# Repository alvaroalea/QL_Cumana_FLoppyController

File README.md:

# Cumana Disk Interface for Sinclair QL

A clone of the Cumana's Floppy Disk Interface for Sinclair QL
(PCB issue 1, ROM version 1.14)

This board has been suessfully tested with ROM 1.16, real floppy disc and gotek.

### The Board

There are two knows version of the ROM, 1.14 and 1.16. unknow diferences between revisiones of ROM.

It use the standar stugart conector, so a plain cable can have up to 4 disk drives, that shall be correctly configured as DS0, DS1, DS2 or DS3.

It use a WD1770 disc controller, but is compatible with WD1772 (you can need to configure start speed), WD1773 is not compatible.

Be aware, when install the transistor, is C,B,E with C near the 7805.

Thanks to Minialler from retrowiki for providing me with a board so I can take pictures and check tracks  that allow me to capture the schema.

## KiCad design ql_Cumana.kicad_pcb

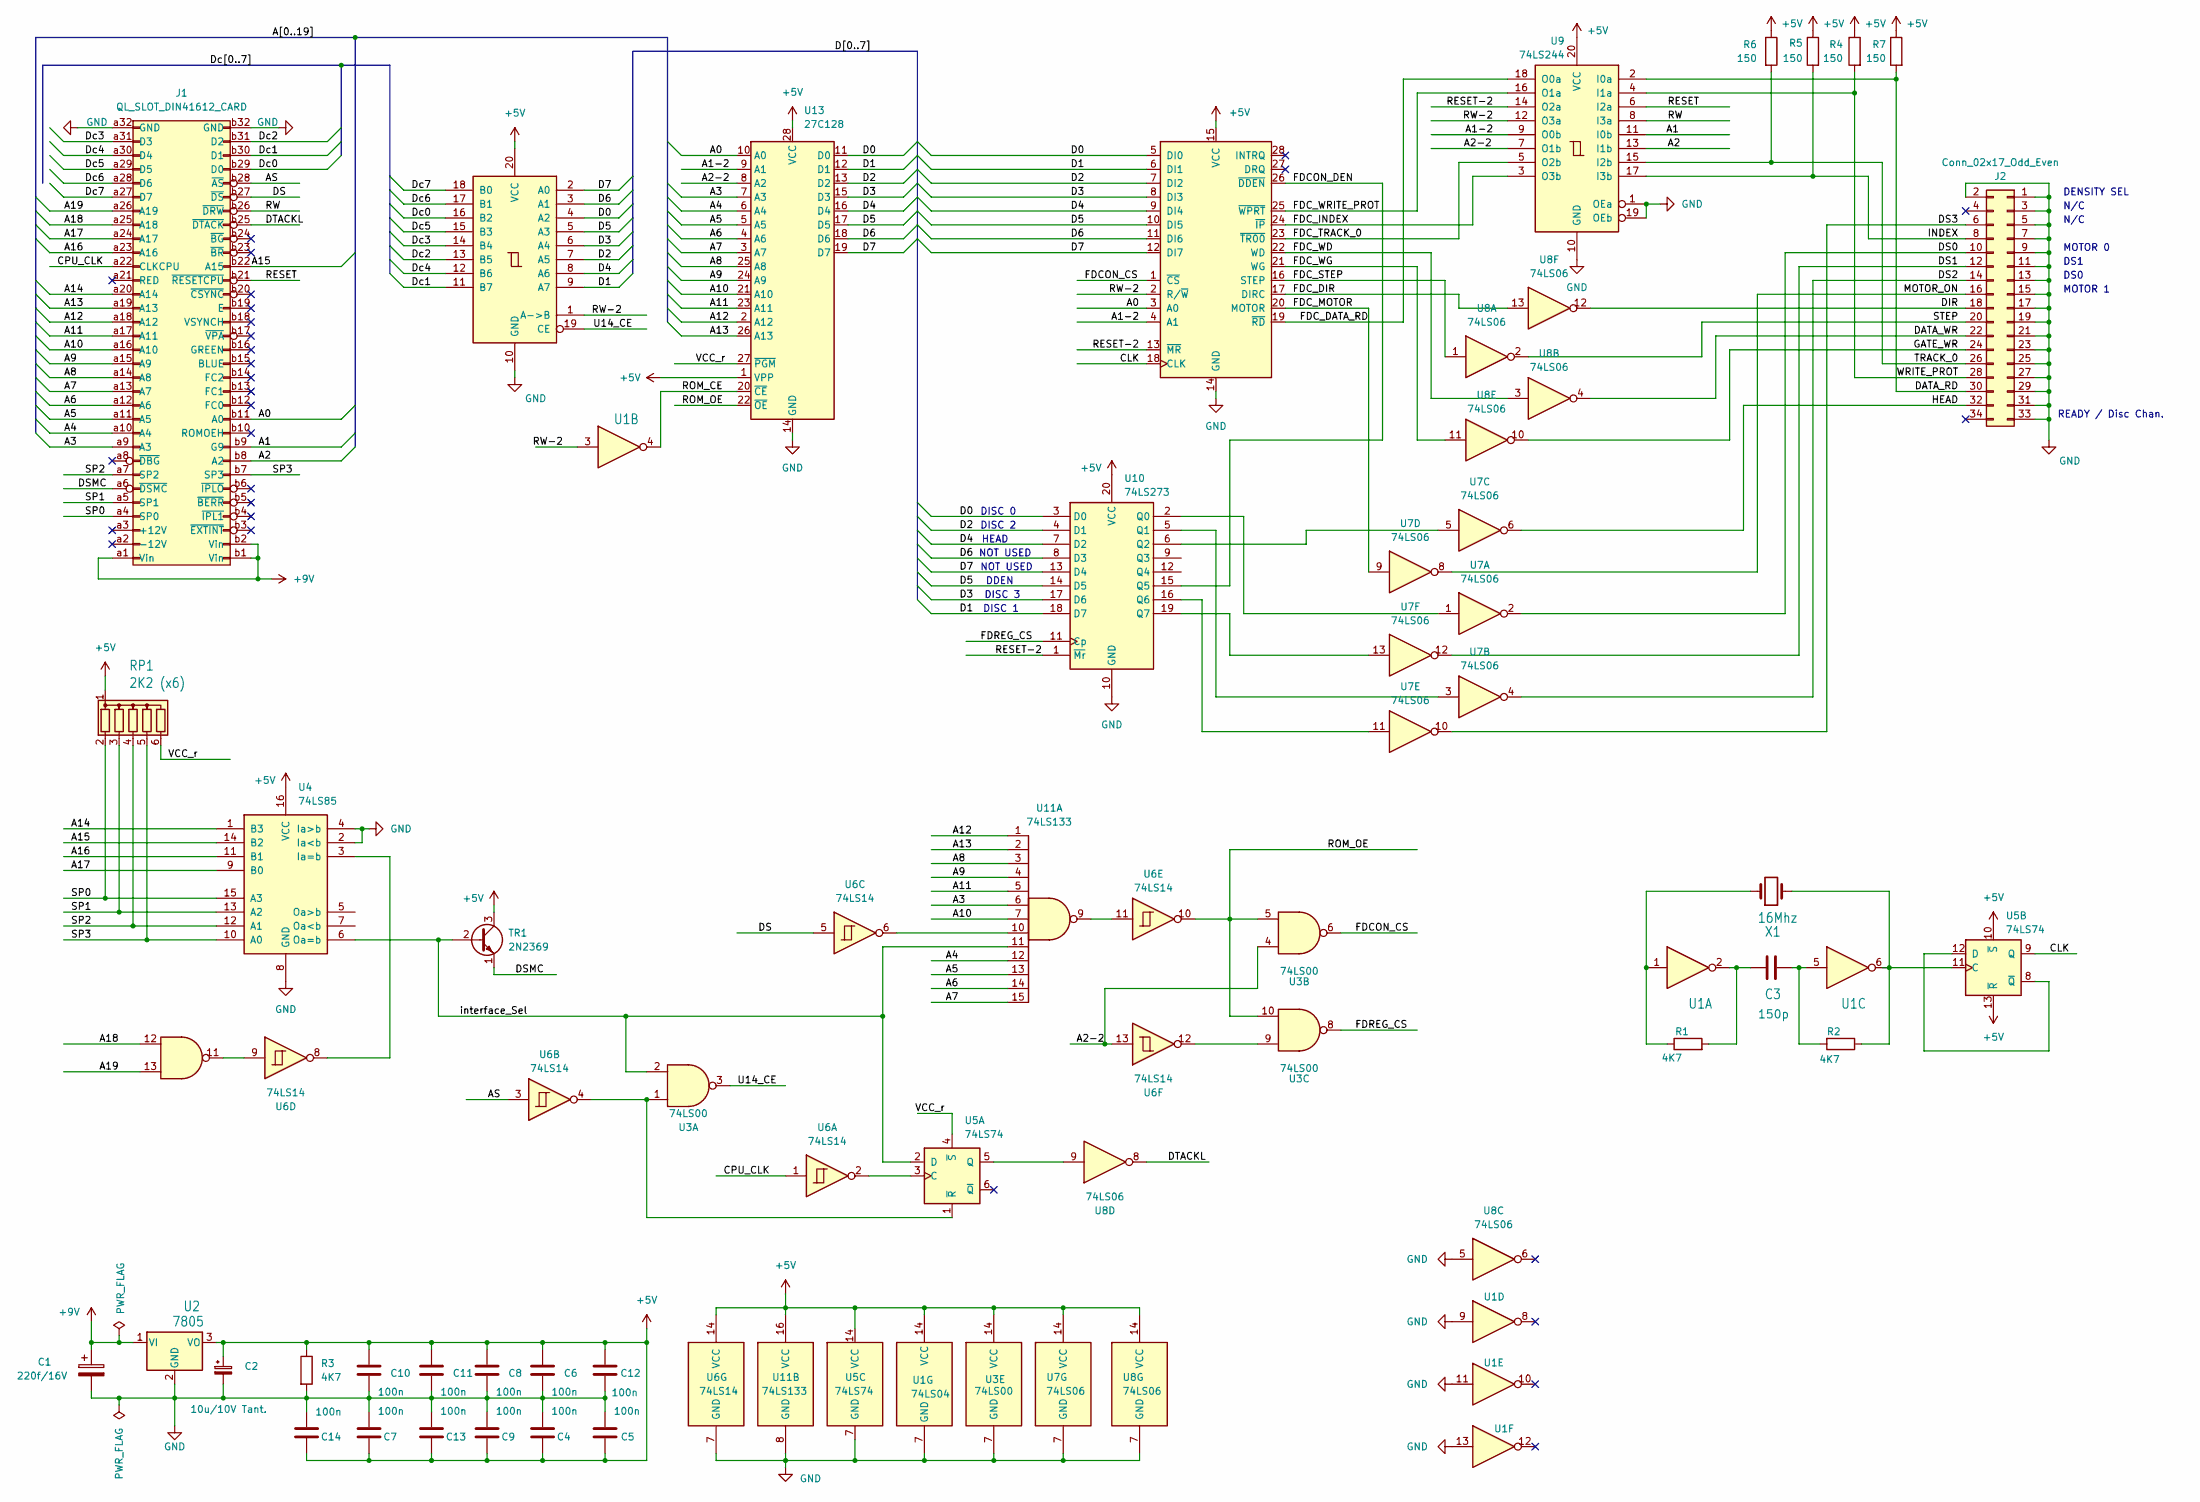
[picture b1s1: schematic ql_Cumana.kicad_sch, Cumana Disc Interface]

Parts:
C1: 220f/16V; CP_Radial_D8.0mm_P5.00mm
C2: 10u/10V Tant.; C_Disc_D7.0mm_W2.5mm_P5.00mm
C3: 150p; C_Disc_D7.0mm_W2.5mm_P5.00mm
C4, C5, C6, C7, C8, C9, C10, C11, C12, C13, C14: 100n; C_Disc_D7.0mm_W2.5mm_P5.00mm
J1: QL_SLOT_DIN41612_CARD; DIN41612_B_2x32_Female_Horizontal_THT
J2: Conn_02x17_Odd_Even; IDC-Header_2x17_P2.54mm_Latch_Horizontal
R1, R2, R3: 4K7; R_Axial_DIN0207_L6.3mm_D2.5mm_P10.16mm_Horizontal
R4, R5, R6, R7: 150; R_Axial_DIN0207_L6.3mm_D2.5mm_P10.16mm_Horizontal
RP1: 2K2 (x6); R_Array_SIP6
TR1: 2N2369; TO-92S_Wide
U1: 74LS04; DIP-14_W7.62mm
U2: 7805; TO-220-3_Horizontal_TabDown
U3: 74LS00; DIP-14_W7.62mm
U4: 74LS85; DIP-16_W7.62mm
U5: 74LS74; DIP-14_W7.62mm
U6: 74LS14; DIP-14_W7.62mm
U7, U8: 74LS06; DIP-14_W7.62mm
U9: 74LS244; DIP-20_W7.62mm
U10: 74LS273; DIP-20_W7.62mm
U11: 74LS133; DIP-16_W7.62mm
U12: FDC_WD1770; DIP-28_W15.24mm_Socket
U13: 27C128; DIP-28_W15.24mm_Socket
U14: 74LS245; DIP-20_W7.62mm
X1: 16Mhz; Crystal_HC18-U_Horizontal

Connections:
+5V: C2.1, C4.1, C5.1, C6.1, C7.1, C8.1, C9.1, C10.1, C11.1, C12.1, C13.1, C14.1, R3.1, R4.1, R5.1, R6.1, R7.1, RP1.1 (common), TR1.3 (C), U1.14 (VCC), U2.3 (VO), U3.14 (VCC), U4.16 (VCC), U5.10 (~S), U5.13 (~R), U5.14 (VCC), U6.14 (VCC), U7.14 (VCC), U8.14 (VCC), U9.20 (VCC), U10.20 (VCC), U11.16 (VCC), U12.15 (VCC), U13.1 (VPP), U13.28 (VCC), U14.20 (VCC)
+9V: C1.1, J1.a1 (Vin), J1.b1 (Vin), J1.b2 (Vin), U2.1 (VI)
/A0: J1.b11 (A0), U12.3 (A0), U13.10 (A0)
/A1: J1.b9 (G9), U9.11 (I0b)
/A1-2: U9.9 (O0b), U12.4 (A1), U13.9 (A1)
/A2: J1.b8 (A2), U9.13 (I1b)
/A2-2: U3.4, U6.13, U9.7 (O1b), U13.8 (A2)
/A3: J1.a9 (A3), U11.6, U13.7 (A3)
/A4: J1.a10 (A4), U11.12, U13.6 (A4)
/A5: J1.a11 (A5), U11.13, U13.5 (A5)
/A6: J1.a12 (A6), U11.14, U13.4 (A6)
/A7: J1.a13 (A7), U11.15, U13.3 (A7)
/A8: J1.a14 (A8), U11.3, U13.25 (A8)
/A9: J1.a15 (A9), U11.4, U13.24 (A9)
/A10: J1.a16 (A10), U11.7, U13.21 (A10)
/A11: J1.a17 (A11), U11.5, U13.23 (A11)
/A12: J1.a18 (A12), U11.1, U13.2 (A12)
/A13: J1.a19 (A13), U11.2, U13.26 (A13)
/A14: J1.a20 (A14), U4.1 (B3)
/A15: J1.b22 (A15), U4.14 (B2)
/A16: J1.a23 (A16), U4.11 (B1)
/A17: J1.a24 (A17), U4.9 (B0)
/A18: J1.a25 (A18), U3.12
/A19: J1.a26 (A19), U3.13
/AS: J1.b28 (~AS), U6.3
/CLK: U5.9 (Q), U12.18 (CLK)
/CPU_CLK: J1.a22 (CLKCPU), U6.1
/D0: U10.3 (D0), U12.5 (DI0), U13.11 (D0), U14.4 (A2)
/D1: U10.18 (D7), U12.6 (DI1), U13.12 (D1), U14.9 (A7)
/D2: U10.4 (D1), U12.7 (DI2), U13.13 (D2), U14.7 (A5)
/D3: U10.17 (D6), U12.8 (DI3), U13.15 (D3), U14.6 (A4)
/D4: U10.7 (D2), U12.9 (DI4), U13.16 (D4), U14.8 (A6)
/D5: U10.14 (D5), U12.10 (DI5), U13.17 (D5), U14.5 (A3)
/D6: U10.8 (D3), U12.11 (DI6), U13.18 (D6), U14.3 (A1)
/D7: U10.13 (D4), U12.12 (DI7), U13.19 (D7), U14.2 (A0)
/DATA_RD: J2.30, R7.2, U9.2 (I0a)
/DATA_WR: J2.22, U8.4
/DIR: J2.18, U8.12
/DS: J1.b27 (~DS), U6.5
/DS0: J2.10, U7.2
/DS1: J2.12, U7.12
/DS2: J2.14, U7.4
/DS3: J2.6, U7.10
/DSMC: J1.a6 (~DSMC), TR1.1 (E)
/DTACKL: J1.b25 (~DTACK), U8.8
/Dc0: J1.b29 (D0), U14.16 (B2)
/Dc1: J1.b30 (D1), U14.11 (B7)
/Dc2: J1.b31 (D2), U14.13 (B5)
/Dc3: J1.a31 (D3), U14.14 (B4)
/Dc4: J1.a30 (D4), U14.12 (B6)
/Dc5: J1.a29 (D5), U14.15 (B3)
/Dc6: J1.a28 (D6), U14.17 (B1)
/Dc7: J1.a27 (D7), U14.18 (B0)
/FDCON_CS: U3.6, U12.1 (~CS)
/FDCON_DEN: U10.15 (Q5), U12.26 (~DDEN)
/FDC_DATA_RD: U9.18 (O0a), U12.19 (~RD)
/FDC_DIR: U8.13, U12.17 (DIRC)
/FDC_INDEX: U9.3 (O3b), U12.24 (~IP)
/FDC_MOTOR: U7.9, U12.20 (MOTOR)
/FDC_STEP: U8.1, U12.16 (STEP)
/FDC_TRACK_0: U9.5 (O2b), U12.23 (~TR00)
/FDC_WD: U8.3, U12.22 (WD)
/FDC_WG: U8.11, U12.21 (WG)
/FDC_WRITE_PROT: U9.16 (O1a), U12.25 (~WPRT)
/FDREG_CS: U3.8, U10.11 (Cp)
/GATE_WR: J2.24, U8.10
/HEAD: J2.32, U7.6
/INDEX: J2.8, R5.2, U9.17 (I3b)
/MOTOR_ON: J2.16, U7.8
/RESET: J1.b21 (~RESETCPU), U9.6 (I2a)
/RESET-2: U9.14 (O2a), U10.1 (~Mr), U12.13 (~MR)
/ROM_CE: U1.4, U13.20 (~CE)
/ROM_OE: U3.5, U3.10, U6.10, U13.22 (~OE)
/RW: J1.b26 (~DRW), U9.8 (I3a)
/RW-2: U1.3, U9.12 (O3a), U12.2 (R/~W), U14.1 (A->B)
/SP0: J1.a4 (SP0), RP1.2 (R1), U4.15 (A3)
/SP1: J1.a5 (SP1), RP1.3 (R2), U4.13 (A2)
/SP2: J1.a7 (SP2), RP1.4 (R3), U4.12 (A1)
/SP3: J1.b7 (SP3), RP1.5 (R4), U4.10 (A0)
/STEP: J2.20, U8.2
/TRACK_0: J2.26, R6.2, U9.15 (I2b)
/U14_CE: U3.3, U14.19 (CE)
/VCC_r: RP1.6 (R5), U5.4 (~S), U13.27 (~PGM)
/WRITE_PROT: J2.28, R4.2, U9.4 (I1a)
/interface_Sel: TR1.2 (B), U3.2, U4.6 (Oa=b), U5.2 (D), U11.11
GND: C1.2, C2.2, C4.2, C5.2, C6.2, C7.2, C8.2, C9.2, C10.2, C11.2, C12.2, C13.2, C14.2, J1.a32 (GND), J1.b32 (GND), J2.1, J2.2, J2.3, J2.5, J2.7, J2.9, J2.11, J2.13, J2.15, J2.17, J2.19, J2.21, J2.23, J2.25, J2.27, J2.29, J2.31, J2.33, R3.2, U1.7 (GND), U1.9, U1.11, U1.13, U2.2 (GND), U3.7 (GND), U4.2 (Ia<b), U4.4 (Ia>b), U4.8 (GND), U5.7 (GND), U6.7 (GND), U7.7 (GND), U8.5, U8.7 (GND), U9.1 (OEa), U9.10 (GND), U9.19 (OEb), U10.10 (GND), U11.8 (GND), U12.14 (GND), U13.14 (GND), U14.10 (GND)
unnamed: C3.1, R2.2, U1.5
unnamed: C3.2, R1.2, U1.2
unnamed: R1.1, U1.1, X1.1
unnamed: U3.9, U6.12
unnamed: U3.11, U6.9
unnamed: U4.3 (Ia=b), U6.8
unnamed: U5.3 (C), U6.2
unnamed: U5.5 (Q), U8.9
unnamed: U3.1, U5.1 (~R), U6.4
unnamed: R2.1, U1.6, U5.11 (C), X1.2
unnamed: U5.8 (~Q), U5.12 (D)
unnamed: U7.1, U10.2 (Q0)
unnamed: U7.3, U10.5 (Q1)
unnamed: U7.5, U10.6 (Q2)
unnamed: U7.11, U10.16 (Q6)
unnamed: U7.13, U10.19 (Q7)
unnamed: U6.11, U11.9
unnamed: U6.6, U11.10

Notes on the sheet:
NOT USED
MOTOR 0
HEAD
DS0
DS1
READY / Disc Chan.
DDEN
DISC 3
MOTOR 1
N/C
DISC 2
DISC 1
DENSITY SEL
DISC 0

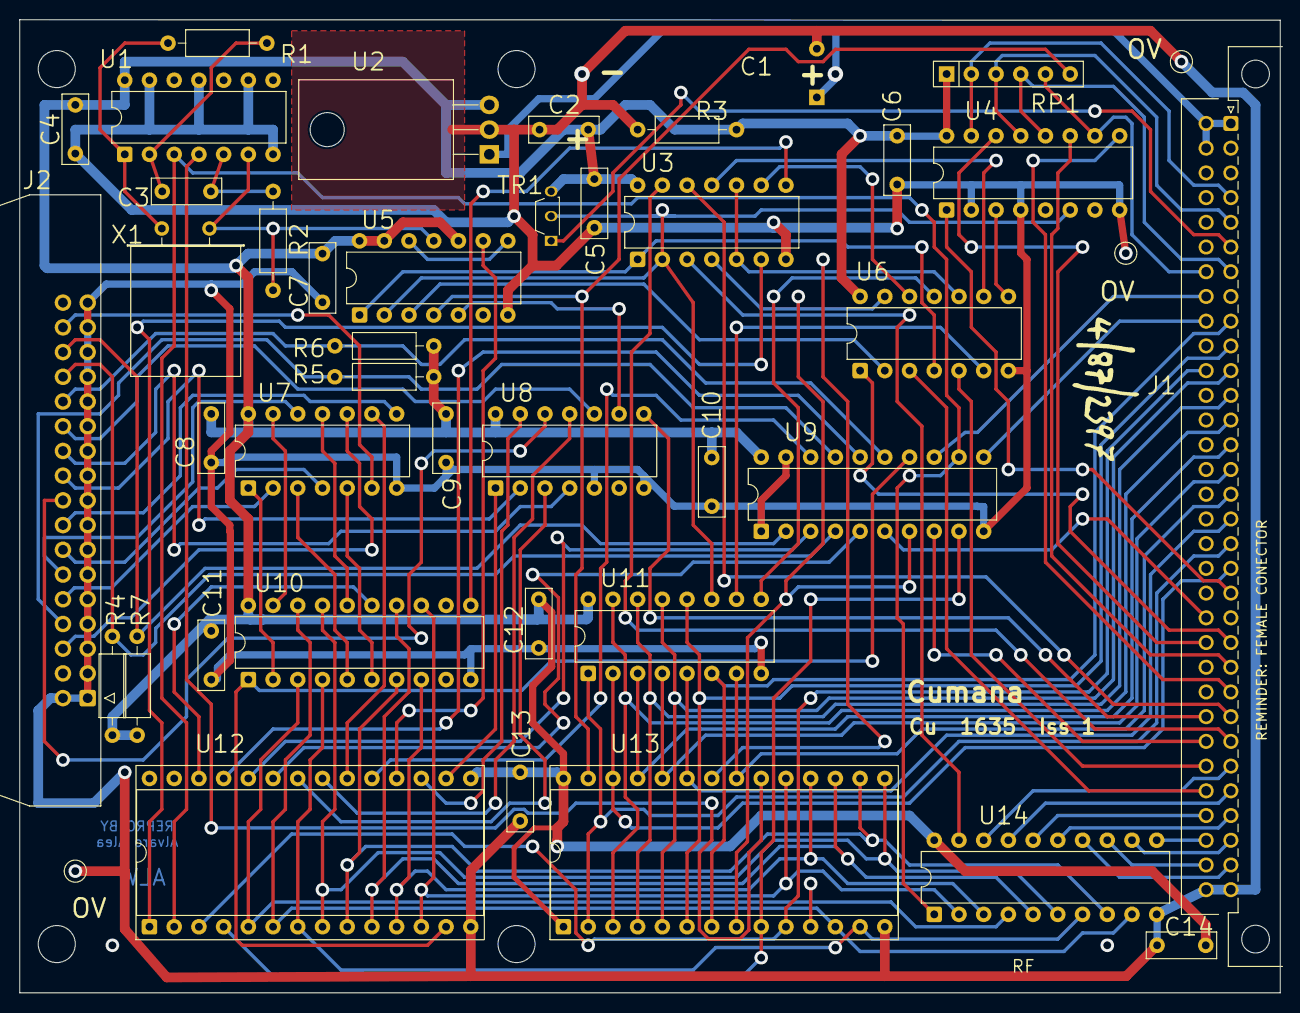
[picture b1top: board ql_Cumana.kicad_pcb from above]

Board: 2 copper layers, 129.5 x 100.0 mm, 40 parts (0 on the bottom side), 104 nets.

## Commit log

2025-04-30 Initial
2025-05-02 fix size and add 3D case
2025-05-03 small size fix
2025-05-08 update silkscreen
2025-06-08 update component values
2026-03-27 complete

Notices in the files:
ql_Cumana.kicad_pcb:
Licensed under Cern OHL-S
